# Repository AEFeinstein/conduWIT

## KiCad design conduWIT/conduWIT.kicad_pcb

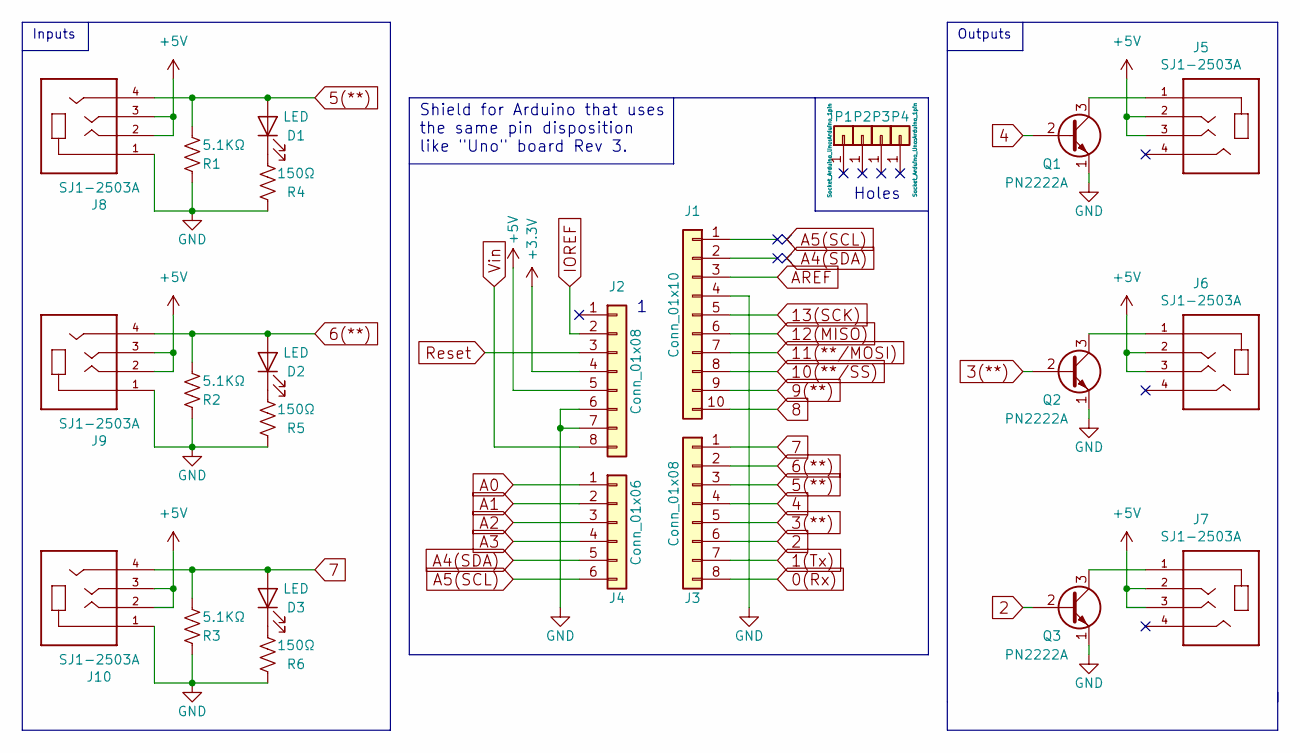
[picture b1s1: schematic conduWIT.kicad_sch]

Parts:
D1, D2, D3: LED; LED_D5.0mm; Digikey 732-5016-ND
J1: Conn_01x10; Socket_Strip_Arduino_1x10; Digikey 2057-PH1-10-UA-ND
J2, J3: Conn_01x08; Socket_Strip_Arduino_1x08; Digikey 2057-PH1-08-UA-ND
J4: Conn_01x06; Socket_Strip_Arduino_1x06; Digikey 2057-PH1-06-UA-ND
J5, J6, J7, J8, J9, J10: SJ1-2503A; CUI_SJ1-2503A; Digikey CP1-2503A-ND
P1, P2, P3, P4: CONN_01X01; Arduino_1pin
Q1, Q2, Q3: PN2222A; TO-92_Inline; Digikey PN2222ATACT-ND
R1, R2, R3: 5.1KΩ; R_Axial_DIN0207_L6.3mm_D2.5mm_P7.62mm_Horizontal; Digikey S5.1KCACT-ND
R4, R5, R6: 150Ω; R_Axial_DIN0207_L6.3mm_D2.5mm_P7.62mm_Horizontal; Digikey S150CACT-ND

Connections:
0(Rx): J3.8
1(Tx): J3.7
2: J3.6, Q3.2 (B)
3(**): J3.5, Q2.2 (B)
4: J3.4, Q1.2 (B)
5(**): D1.2 (A), J3.3, J8.4, R1.2
6(**): D2.2 (A), J3.2, J9.4, R2.2
7: D3.2 (A), J3.1, J10.4, R3.2
8: J1.10
9(**): J1.9
10(**/SS): J1.8
11(**/MOSI): J1.7
12(MISO): J1.6
13(SCK): J1.5
+3.3V: J2.4
+5V: J2.5, J5.2, J5.3, J6.2, J6.3, J7.2, J7.3, J8.2, J8.3, J9.2, J9.3, J10.2, J10.3
A0: J4.1
A1: J4.2
A2: J4.3
A3: J4.4
A4(SDA): J4.5
A5(SCL): J4.6
AREF: J1.3
GND: J1.4, J2.6, J2.7, J8.1, J9.1, J10.1, Q1.1 (E), Q2.1 (E), Q3.1 (E), R1.1, R2.1, R3.1, R4.1, R5.1, R6.1
IOREF: J2.2
unnamed: D1.1 (K), R4.2
unnamed: D2.1 (K), R5.2
unnamed: D3.1 (K), R6.2
unnamed: J5.1, Q1.3 (C)
unnamed: J6.1, Q2.3 (C)
unnamed: J7.1, Q3.3 (C)
Reset: J2.3
Vin: J2.8

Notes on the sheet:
Shield for Arduino that uses the same pin disposition like "Uno" board Rev 3.
Inputs
Holes
Outputs

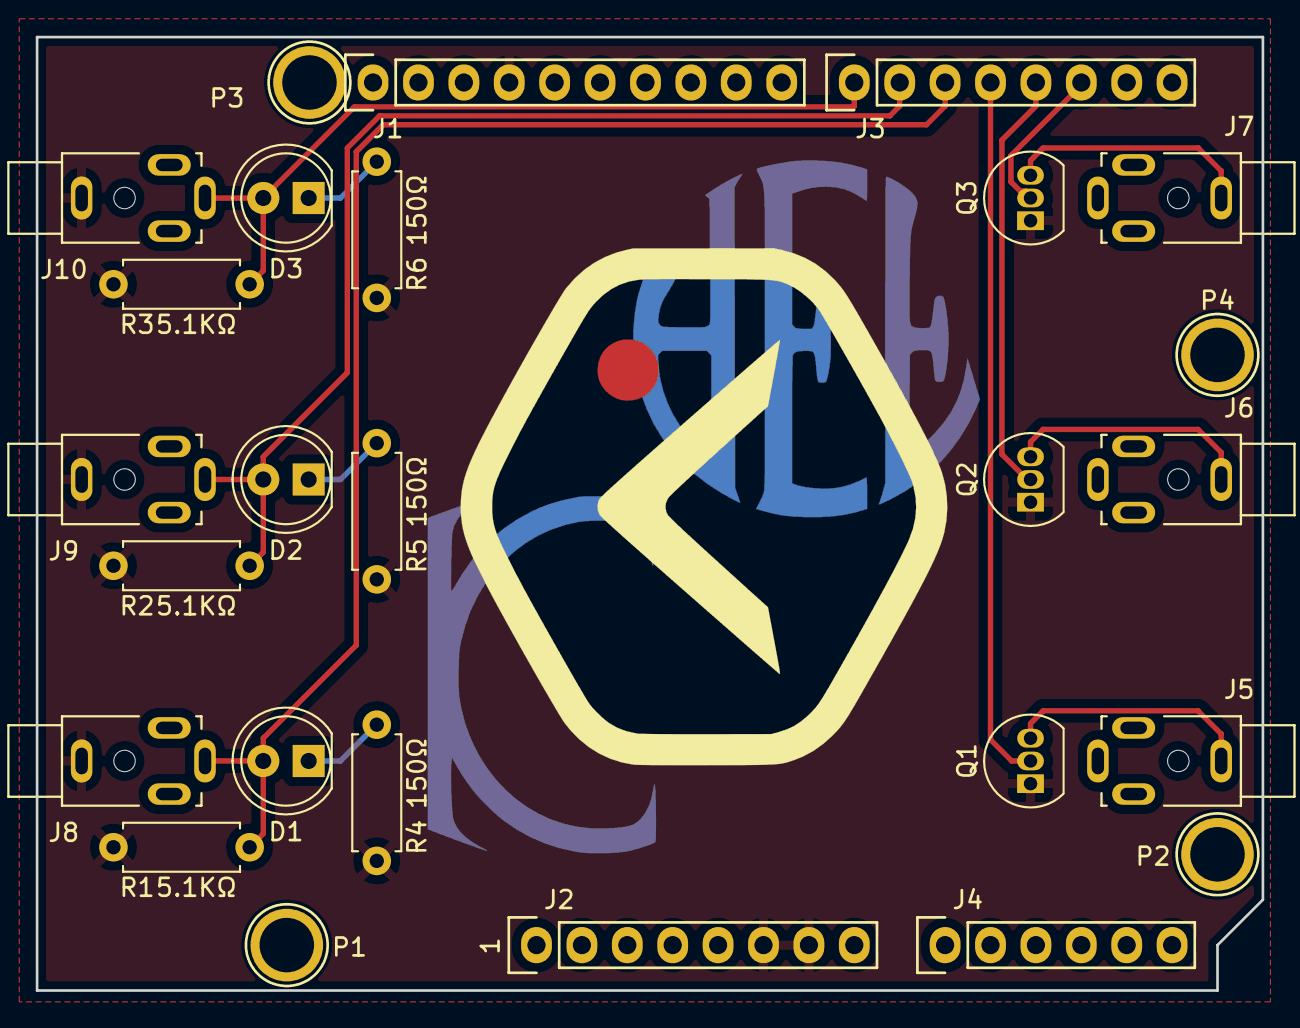
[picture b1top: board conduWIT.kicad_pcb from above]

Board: 2 copper layers, 68.6 x 53.3 mm, 28 parts (1 on the bottom side), 14 nets.

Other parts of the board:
Ref**: Val**; adc
Ref**#2: Val**; signatures

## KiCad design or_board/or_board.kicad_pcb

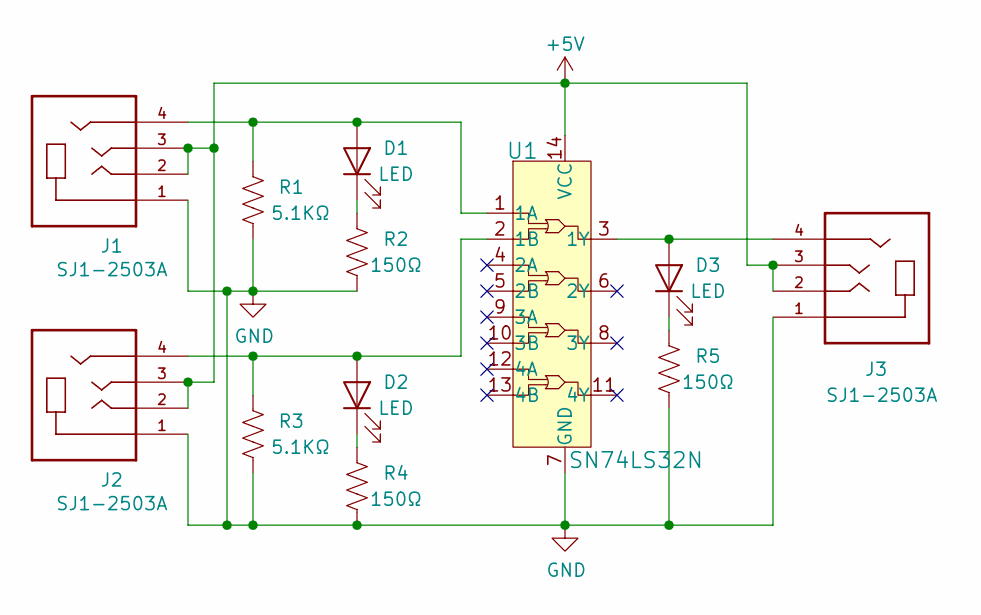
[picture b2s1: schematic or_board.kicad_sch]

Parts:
D1, D2, D3: LED; LED_D5.0mm; Digikey 732-5016-ND
J1, J2, J3: SJ1-2503A; CUI_SJ1-2503A; Digikey CP1-2503A-ND
R1, R3: 5.1KΩ; R_Axial_DIN0207_L6.3mm_D2.5mm_P7.62mm_Horizontal; Digikey S5.1KCACT-ND
R2, R4, R5: 150Ω; R_Axial_DIN0207_L6.3mm_D2.5mm_P7.62mm_Horizontal; Digikey S150CACT-ND
U1: SN74LS32N; DIP-14_W3mm; Digikey 296-1658-5-ND

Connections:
+5V: J1.2, J1.3, J2.2, J2.3, J3.2, J3.3, U1.14 (VCC)
GND: J1.1, J2.1, J3.1, R1.1, R2.1, R3.1, R4.1, R5.1, U1.7 (GND)
unnamed: D1.1 (K), R2.2
unnamed: D1.2 (A), J1.4, R1.2, U1.1 (1A)
unnamed: D2.1 (K), R4.2
unnamed: D2.2 (A), J2.4, R3.2, U1.2 (1B)
unnamed: D3.1 (K), R5.2
unnamed: D3.2 (A), J3.4, U1.3 (1Y)

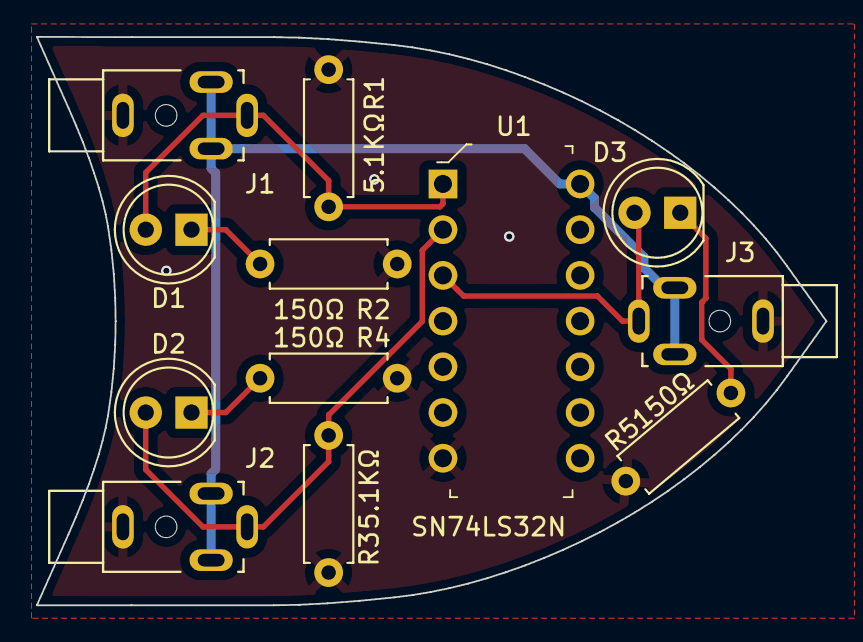
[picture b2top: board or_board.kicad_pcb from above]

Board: 2 copper layers, 43.9 x 31.6 mm, 13 parts (1 on the bottom side), 8 nets.

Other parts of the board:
Ref**: Val**; or_truth_table

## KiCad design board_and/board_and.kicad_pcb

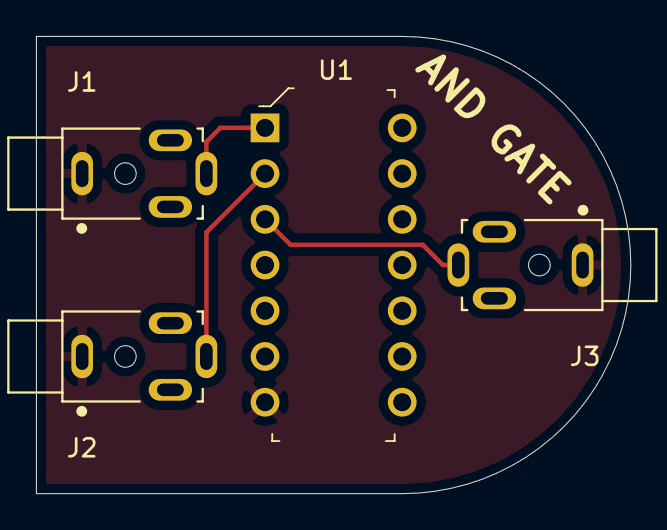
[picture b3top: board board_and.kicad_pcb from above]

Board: 2 copper layers, 33.0 x 25.4 mm, 4 parts (0 on the bottom side), 5 nets.

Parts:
J1, J2, J3: SJ1-2503A; CUI_SJ1-2503A
U1: SN74LS08N; DIP-14_W3mm

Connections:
+5V: J1.2, J1.3, J2.2, J2.3, J3.2, J3.3, U1.14
GND: J1.1, J2.1, J3.1, U1.7
unnamed: J1.4, U1.1
unnamed: J2.4, U1.2
unnamed: J3.4, U1.3

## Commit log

2020-02-04 Added blank slate
2020-02-04 Added logic chips to the repo
2020-02-04 Updated .gitignore
2020-02-04 Added AND gate
2020-02-04 removed AND gate
2020-02-22 Prepped parts
2020-02-22 Updated pin headers
2020-02-26 Cleaned up part silkscreen
2020-02-26 Cleaned up PCB
2020-02-27 Made schematic and layout
2020-02-27 Cleaned up layout
2020-02-27 Art! Also cleaned up layout
2020-02-27 Updated library parts
2020-02-27 Updated art files
2020-03-04 Added 'and' board
2020-03-05 Added 'or' board
2020-03-05 Updated outline for 'and' board
2020-03-05 Changed outline for 'and' board
2020-03-05 Modified silkscreen
2020-03-05 PCB tweaks
2020-03-09 Added truth table silk to and/or boards
2020-03-09 Added ADC logo
2020-03-13 Added signatures Added name, version, date
2020-03-16 Increased track width and clearance
2020-03-16 Final silkscreen touch-up
2023-01-24 Update resistor values, clean schematic
2023-01-24 Updated OR board resistor values
2023-01-24 Readd truth table
2023-01-24 Fix version
2023-01-24 Updated resistor values on ConduWIT
2023-01-25 Clean up schematic
    Fix islands on bottom of PCB
